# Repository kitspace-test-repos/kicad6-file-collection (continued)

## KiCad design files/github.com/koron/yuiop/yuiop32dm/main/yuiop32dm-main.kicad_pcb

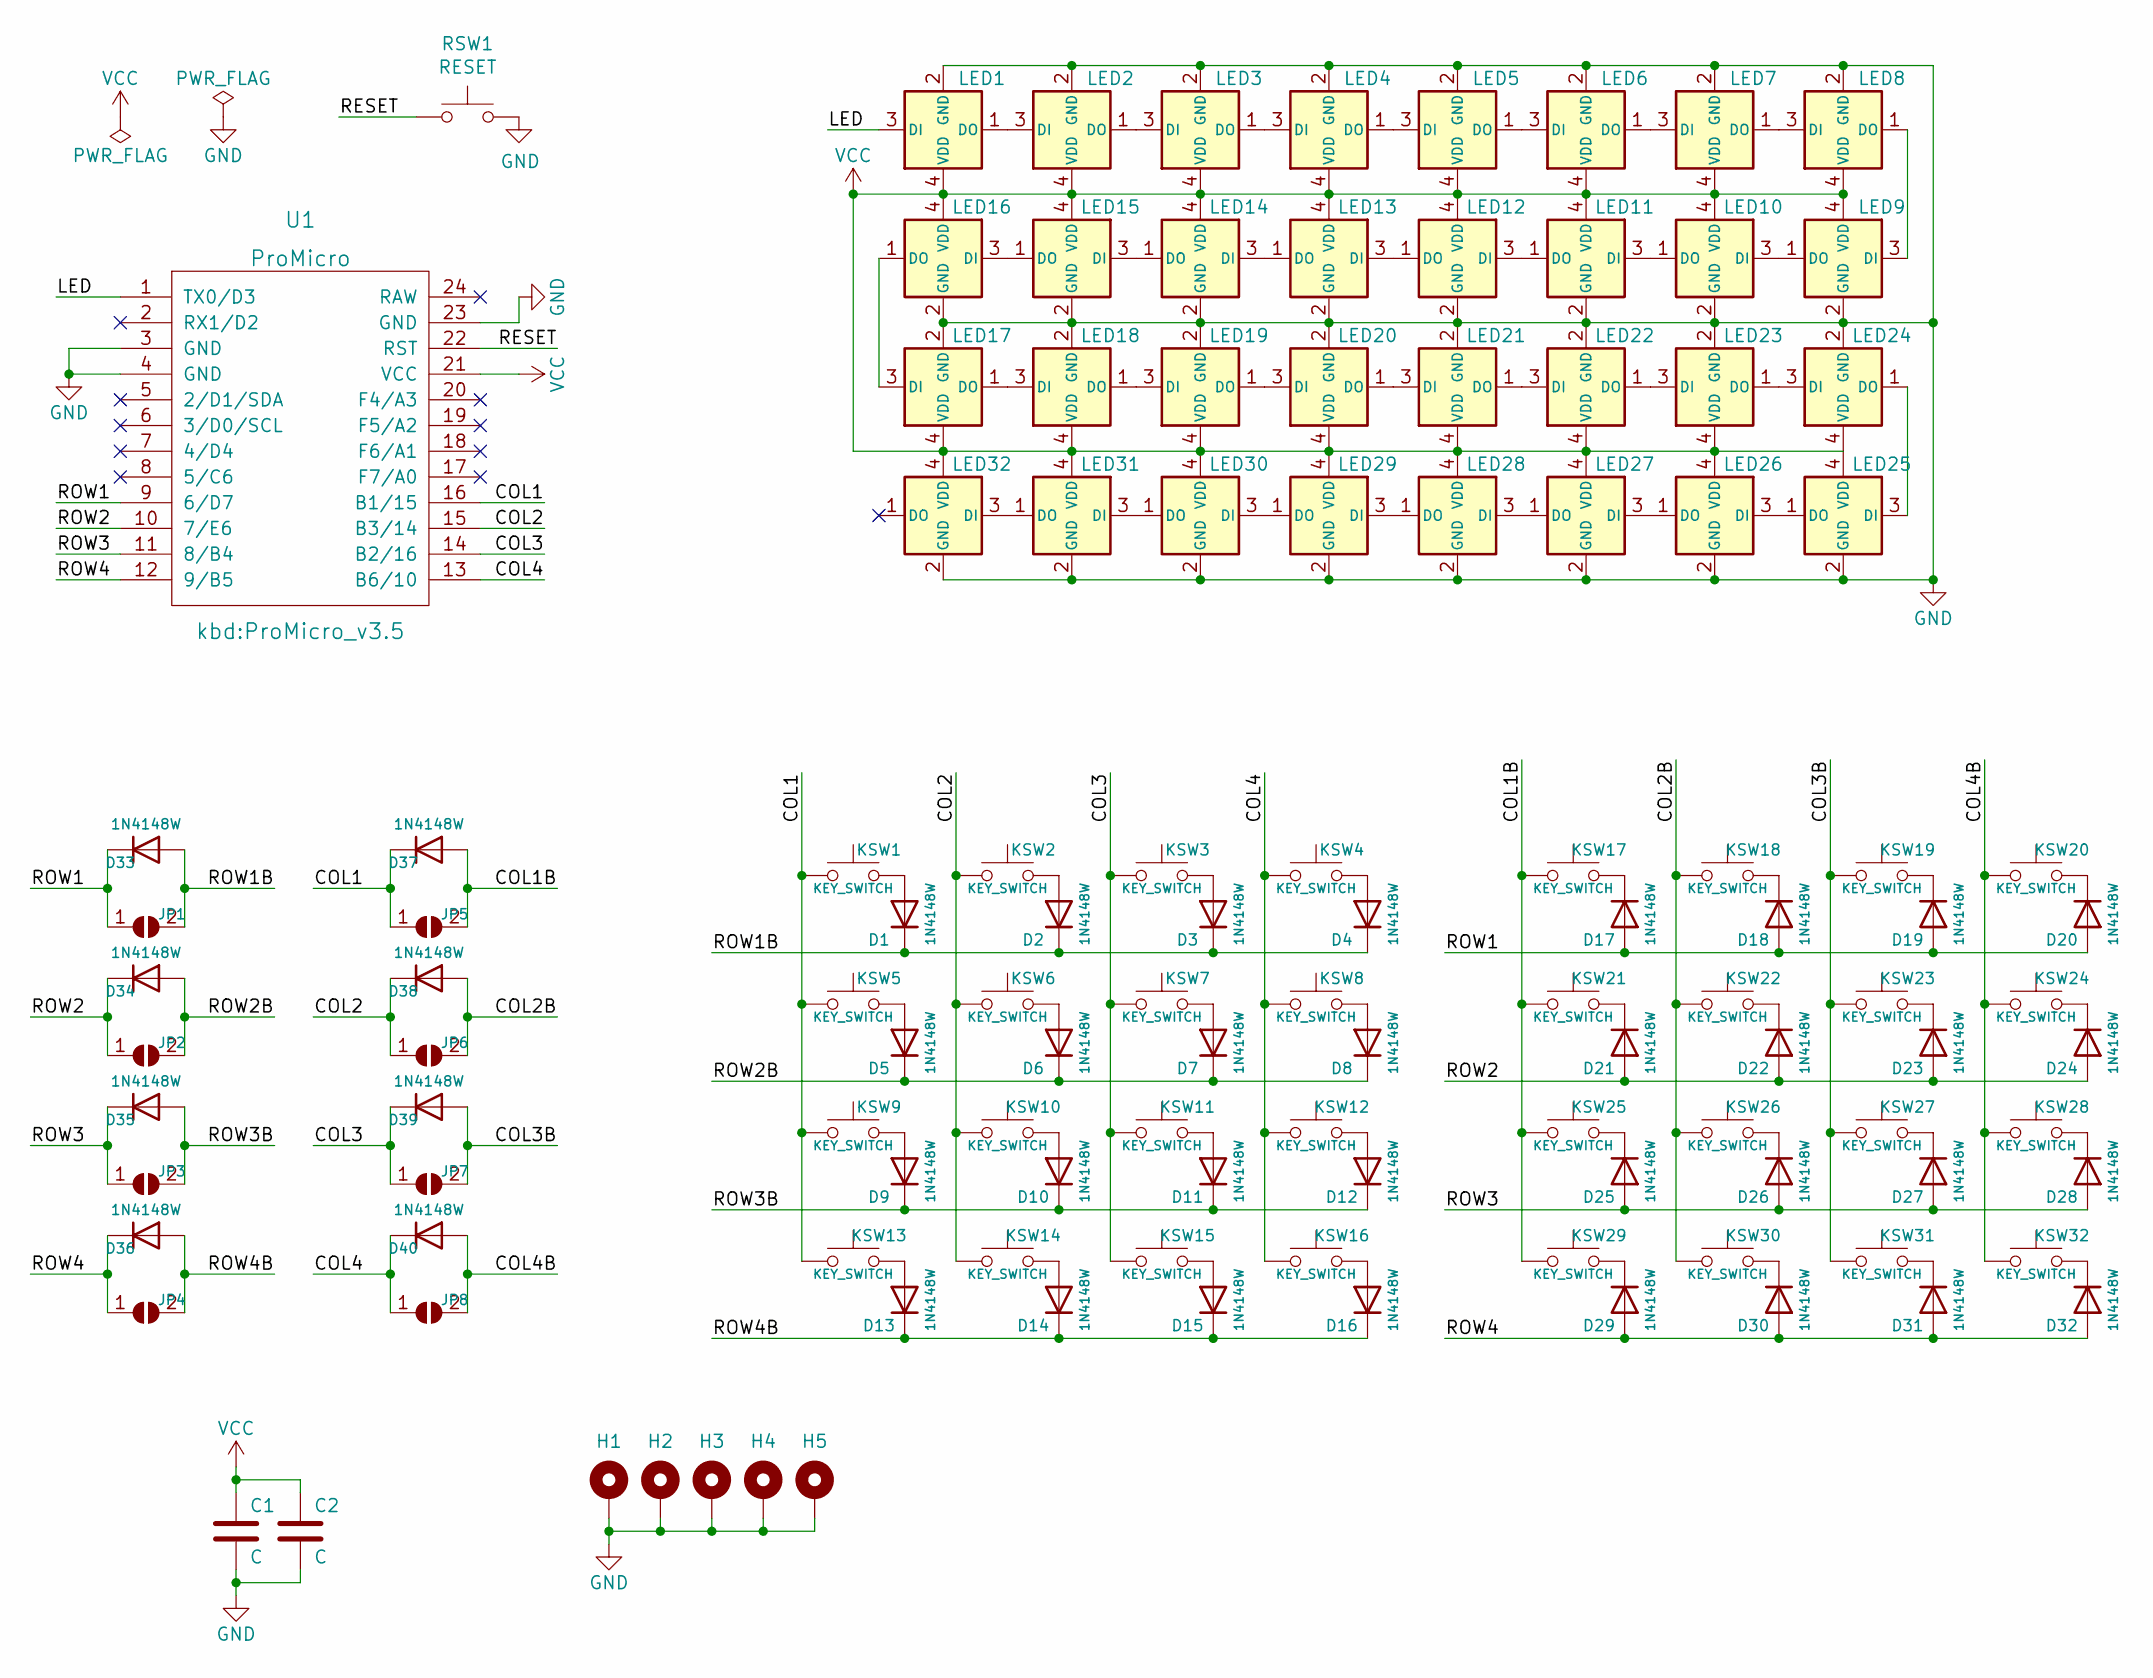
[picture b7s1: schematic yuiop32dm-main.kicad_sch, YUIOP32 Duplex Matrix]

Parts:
C1, C2: C; C_0603_1608Metric_Pad1.08x0.95mm_HandSolder
D1, D2, D3, D4, D5, D6, D7, D8, D9, D10, D11, D12, D13, D14, D15, D16, D17, D18, D19, D20, D21, D22, D23, D24, D25, D26, D27, D28, D29, D30, D31, D32, D33, D34, D35, D36, D37, D38, D39, D40: 1N4148W; D_SOD-123
H1, H2, H3, H4, H5: MountingHole_Pad; Hole_2.2_4
JP1, JP2, JP3, JP4, JP5, JP6, JP7, JP8: SolderJumper_2_Open; SolderJumper-2_P1.3mm_Open_RoundedPad1.0x1.5mm
KSW1, KSW2, KSW3, KSW4, KSW5, KSW6, KSW7, KSW8, KSW9, KSW10, KSW11, KSW12, KSW13, KSW14, KSW15, KSW16, KSW17, KSW18, KSW19, KSW20, KSW21, KSW22, KSW23, KSW24, KSW25, KSW26, KSW27, KSW28, KSW29, KSW30, KSW31, KSW32: KEY_SWITCH; Cherry_MX_Hotswap_1.0u_v3
LED1, LED2, LED3, LED4, LED5, LED6, LED7, LED8, LED9, LED10, LED11, LED12, LED13, LED14, LED15, LED16, LED17, LED18, LED19, LED20, LED21, LED22, LED23, LED24, LED25, LED26, LED27, LED28, LED29, LED30, LED31, LED32: WS2812C-2020; LED_WS2812C-2020_BackMount_v2
RSW1: RESET; ResetSW_2_1side
U1: ProMicro; ProMicro_v3.5

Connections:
/COL1: D37.1 (K), JP5.1 (A), KSW1.1, KSW5.1, KSW9.1, KSW13.1, U1.16 (B1/15)
/COL1B: D37.2 (A), JP5.2 (B), KSW17.1, KSW21.1, KSW25.1, KSW29.1
/COL2: D38.1 (K), JP6.1 (A), KSW2.1, KSW6.1, KSW10.1, KSW14.1, U1.15 (B3/14)
/COL2B: D38.2 (A), JP6.2 (B), KSW18.1, KSW22.1, KSW26.1, KSW30.1
/COL3: D39.1 (K), JP7.1 (A), KSW3.1, KSW7.1, KSW11.1, KSW15.1, U1.14 (B2/16)
/COL3B: D39.2 (A), JP7.2 (B), KSW19.1, KSW23.1, KSW27.1, KSW31.1
/COL4: D40.1 (K), JP8.1 (A), KSW4.1, KSW8.1, KSW12.1, KSW16.1, U1.13 (B6/10)
/COL4B: D40.2 (A), JP8.2 (B), KSW20.1, KSW24.1, KSW28.1, KSW32.1
/LED: LED1.3 (DI), U1.1 (TX0/D3)
/RESET: RSW1.1, U1.22 (RST)
/ROW1: D17.2 (A), D18.2 (A), D19.2 (A), D20.2 (A), D33.1 (K), JP1.1 (A), U1.9 (6/D7)
/ROW1B: D1.1 (K), D2.1 (K), D3.1 (K), D4.1 (K), D33.2 (A), JP1.2 (B)
/ROW2: D21.2 (A), D22.2 (A), D23.2 (A), D24.2 (A), D34.1 (K), JP2.1 (A), U1.10 (7/E6)
/ROW2B: D5.1 (K), D6.1 (K), D7.1 (K), D8.1 (K), D34.2 (A), JP2.2 (B)
/ROW3: D25.2 (A), D26.2 (A), D27.2 (A), D28.2 (A), D35.1 (K), JP3.1 (A), U1.11 (8/B4)
/ROW3B: D9.1 (K), D10.1 (K), D11.1 (K), D12.1 (K), D35.2 (A), JP3.2 (B)
/ROW4: D29.2 (A), D30.2 (A), D31.2 (A), D32.2 (A), D36.1 (K), JP4.1 (A), U1.12 (9/B5)
/ROW4B: D13.1 (K), D14.1 (K), D15.1 (K), D16.1 (K), D36.2 (A), JP4.2 (B)
GND: C1.2, C2.2, H1.1, H2.1, H3.1, H4.1, H5.1, LED1.2 (GND), LED2.2 (GND), LED3.2 (GND), LED4.2 (GND), LED5.2 (GND), LED6.2 (GND), LED7.2 (GND), LED8.2 (GND), LED9.2 (GND), LED10.2 (GND), LED11.2 (GND), LED12.2 (GND), LED13.2 (GND), LED14.2 (GND), LED15.2 (GND), LED16.2 (GND), LED17.2 (GND), LED18.2 (GND), LED19.2 (GND), LED20.2 (GND), LED21.2 (GND), LED22.2 (GND), LED23.2 (GND), LED24.2 (GND), LED25.2 (GND), LED26.2 (GND), LED27.2 (GND), LED28.2 (GND), LED29.2 (GND), LED30.2 (GND), LED31.2 (GND), LED32.2 (GND), RSW1.2, U1.3 (GND), U1.4 (GND), U1.23 (GND)
unnamed: D1.2 (A), KSW1.2
unnamed: D2.2 (A), KSW2.2
unnamed: D3.2 (A), KSW3.2
unnamed: D4.2 (A), KSW4.2
unnamed: D5.2 (A), KSW5.2
unnamed: D6.2 (A), KSW6.2
unnamed: D7.2 (A), KSW7.2
unnamed: D8.2 (A), KSW8.2
unnamed: D9.2 (A), KSW9.2
unnamed: D10.2 (A), KSW10.2
unnamed: D11.2 (A), KSW11.2
unnamed: D12.2 (A), KSW12.2
unnamed: D13.2 (A), KSW13.2
unnamed: D14.2 (A), KSW14.2
unnamed: D15.2 (A), KSW15.2
unnamed: D16.2 (A), KSW16.2
unnamed: D17.1 (K), KSW17.2
unnamed: D18.1 (K), KSW18.2
unnamed: D19.1 (K), KSW19.2
unnamed: D20.1 (K), KSW20.2
unnamed: D21.1 (K), KSW21.2
unnamed: D22.1 (K), KSW22.2
unnamed: D23.1 (K), KSW23.2
unnamed: D24.1 (K), KSW24.2
unnamed: D25.1 (K), KSW25.2
unnamed: D26.1 (K), KSW26.2
unnamed: D27.1 (K), KSW27.2
unnamed: D28.1 (K), KSW28.2
unnamed: D29.1 (K), KSW29.2
unnamed: D30.1 (K), KSW30.2
unnamed: D31.1 (K), KSW31.2
unnamed: D32.1 (K), KSW32.2
unnamed: LED1.1 (DO), LED2.3 (DI)
unnamed: LED2.1 (DO), LED3.3 (DI)
unnamed: LED3.1 (DO), LED4.3 (DI)
unnamed: LED4.1 (DO), LED5.3 (DI)
unnamed: LED5.1 (DO), LED6.3 (DI)
unnamed: LED6.1 (DO), LED7.3 (DI)
unnamed: LED7.1 (DO), LED8.3 (DI)
unnamed: LED8.1 (DO), LED9.3 (DI)
unnamed: LED10.1 (DO), LED11.3 (DI)
unnamed: LED9.1 (DO), LED10.3 (DI)
unnamed: LED11.1 (DO), LED12.3 (DI)
unnamed: LED12.1 (DO), LED13.3 (DI)
unnamed: LED13.1 (DO), LED14.3 (DI)
unnamed: LED14.1 (DO), LED15.3 (DI)
unnamed: LED15.1 (DO), LED16.3 (DI)
unnamed: LED16.1 (DO), LED17.3 (DI)
unnamed: LED17.1 (DO), LED18.3 (DI)
unnamed: LED18.1 (DO), LED19.3 (DI)
unnamed: LED19.1 (DO), LED20.3 (DI)
unnamed: LED20.1 (DO), LED21.3 (DI)
unnamed: LED21.1 (DO), LED22.3 (DI)
unnamed: LED22.1 (DO), LED23.3 (DI)
unnamed: LED23.1 (DO), LED24.3 (DI)
unnamed: LED24.1 (DO), LED25.3 (DI)
unnamed: LED25.1 (DO), LED26.3 (DI)
unnamed: LED26.1 (DO), LED27.3 (DI)
unnamed: LED27.1 (DO), LED28.3 (DI)
unnamed: LED28.1 (DO), LED29.3 (DI)
unnamed: LED29.1 (DO), LED30.3 (DI)
unnamed: LED30.1 (DO), LED31.3 (DI)
unnamed: LED31.1 (DO), LED32.3 (DI)
VCC: C1.1, C2.1, LED1.4 (VDD), LED2.4 (VDD), LED3.4 (VDD), LED4.4 (VDD), LED5.4 (VDD), LED6.4 (VDD), LED7.4 (VDD), LED8.4 (VDD), LED9.4 (VDD), LED10.4 (VDD), LED11.4 (VDD), LED12.4 (VDD), LED13.4 (VDD), LED14.4 (VDD), LED15.4 (VDD), LED16.4 (VDD), LED17.4 (VDD), LED18.4 (VDD), LED19.4 (VDD), LED20.4 (VDD), LED21.4 (VDD), LED22.4 (VDD), LED23.4 (VDD), LED24.4 (VDD), LED25.4 (VDD), LED26.4 (VDD), LED27.4 (VDD), LED28.4 (VDD), LED29.4 (VDD), LED30.4 (VDD), LED31.4 (VDD), LED32.4 (VDD), U1.21 (VCC)

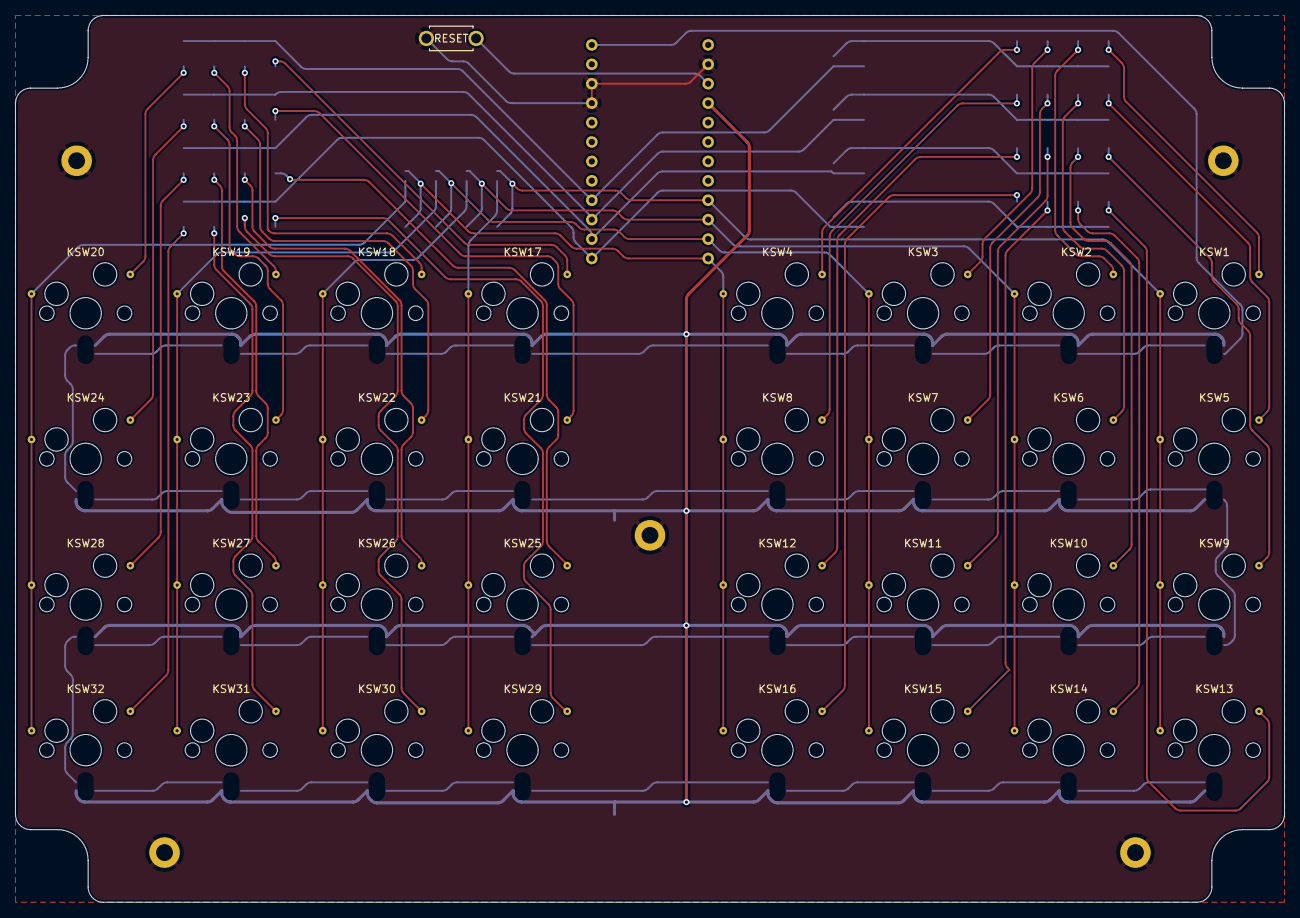
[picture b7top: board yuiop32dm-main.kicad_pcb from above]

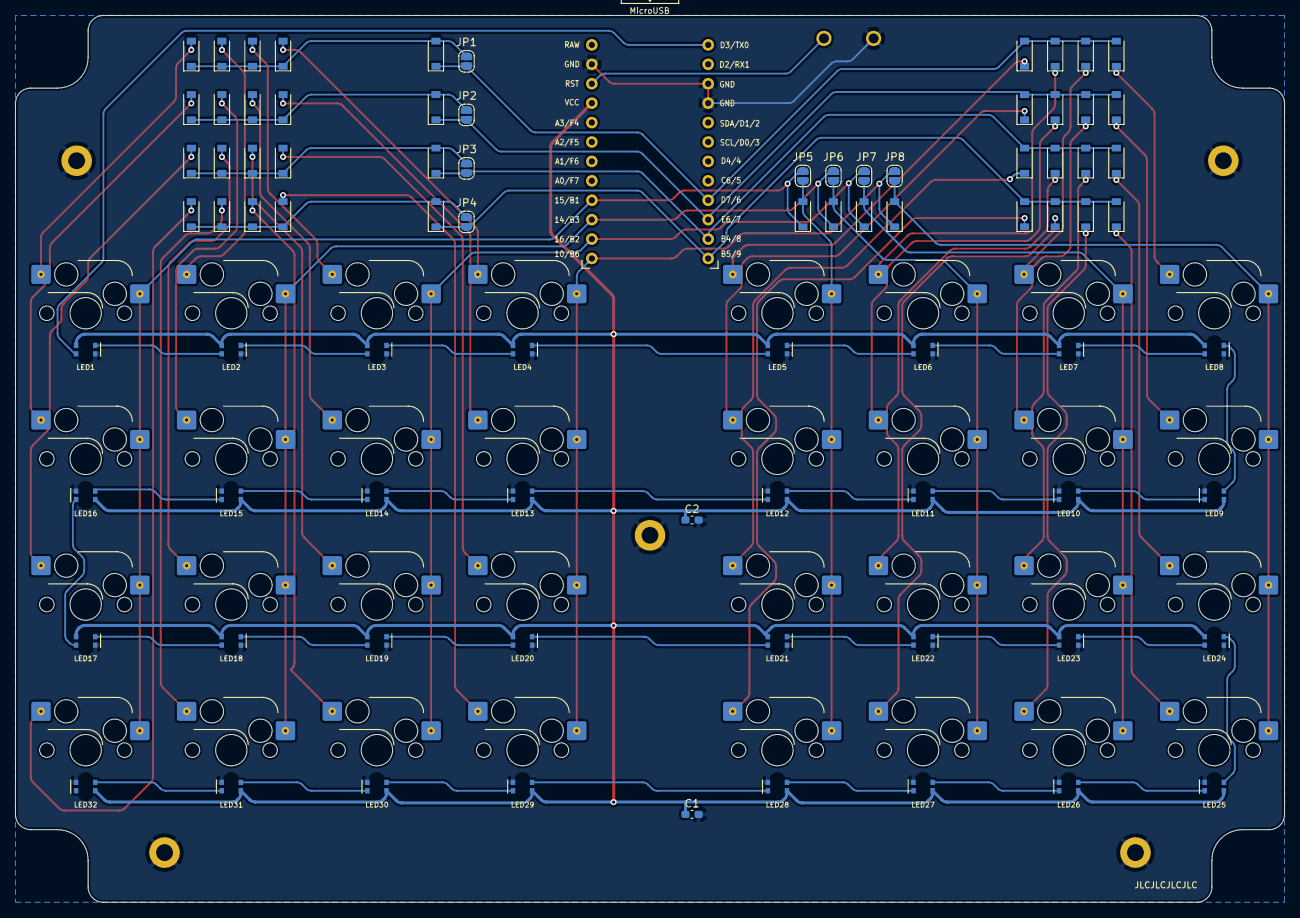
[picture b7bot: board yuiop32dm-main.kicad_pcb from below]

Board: 2 copper layers, 166.0 x 116.0 mm, 121 parts (11 on the bottom side), 83 nets.
